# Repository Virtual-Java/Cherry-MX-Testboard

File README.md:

# Cherry-MX-Testboard
A simple single-sided testboard for Cherry-MX-Switches created with EAGLE layout

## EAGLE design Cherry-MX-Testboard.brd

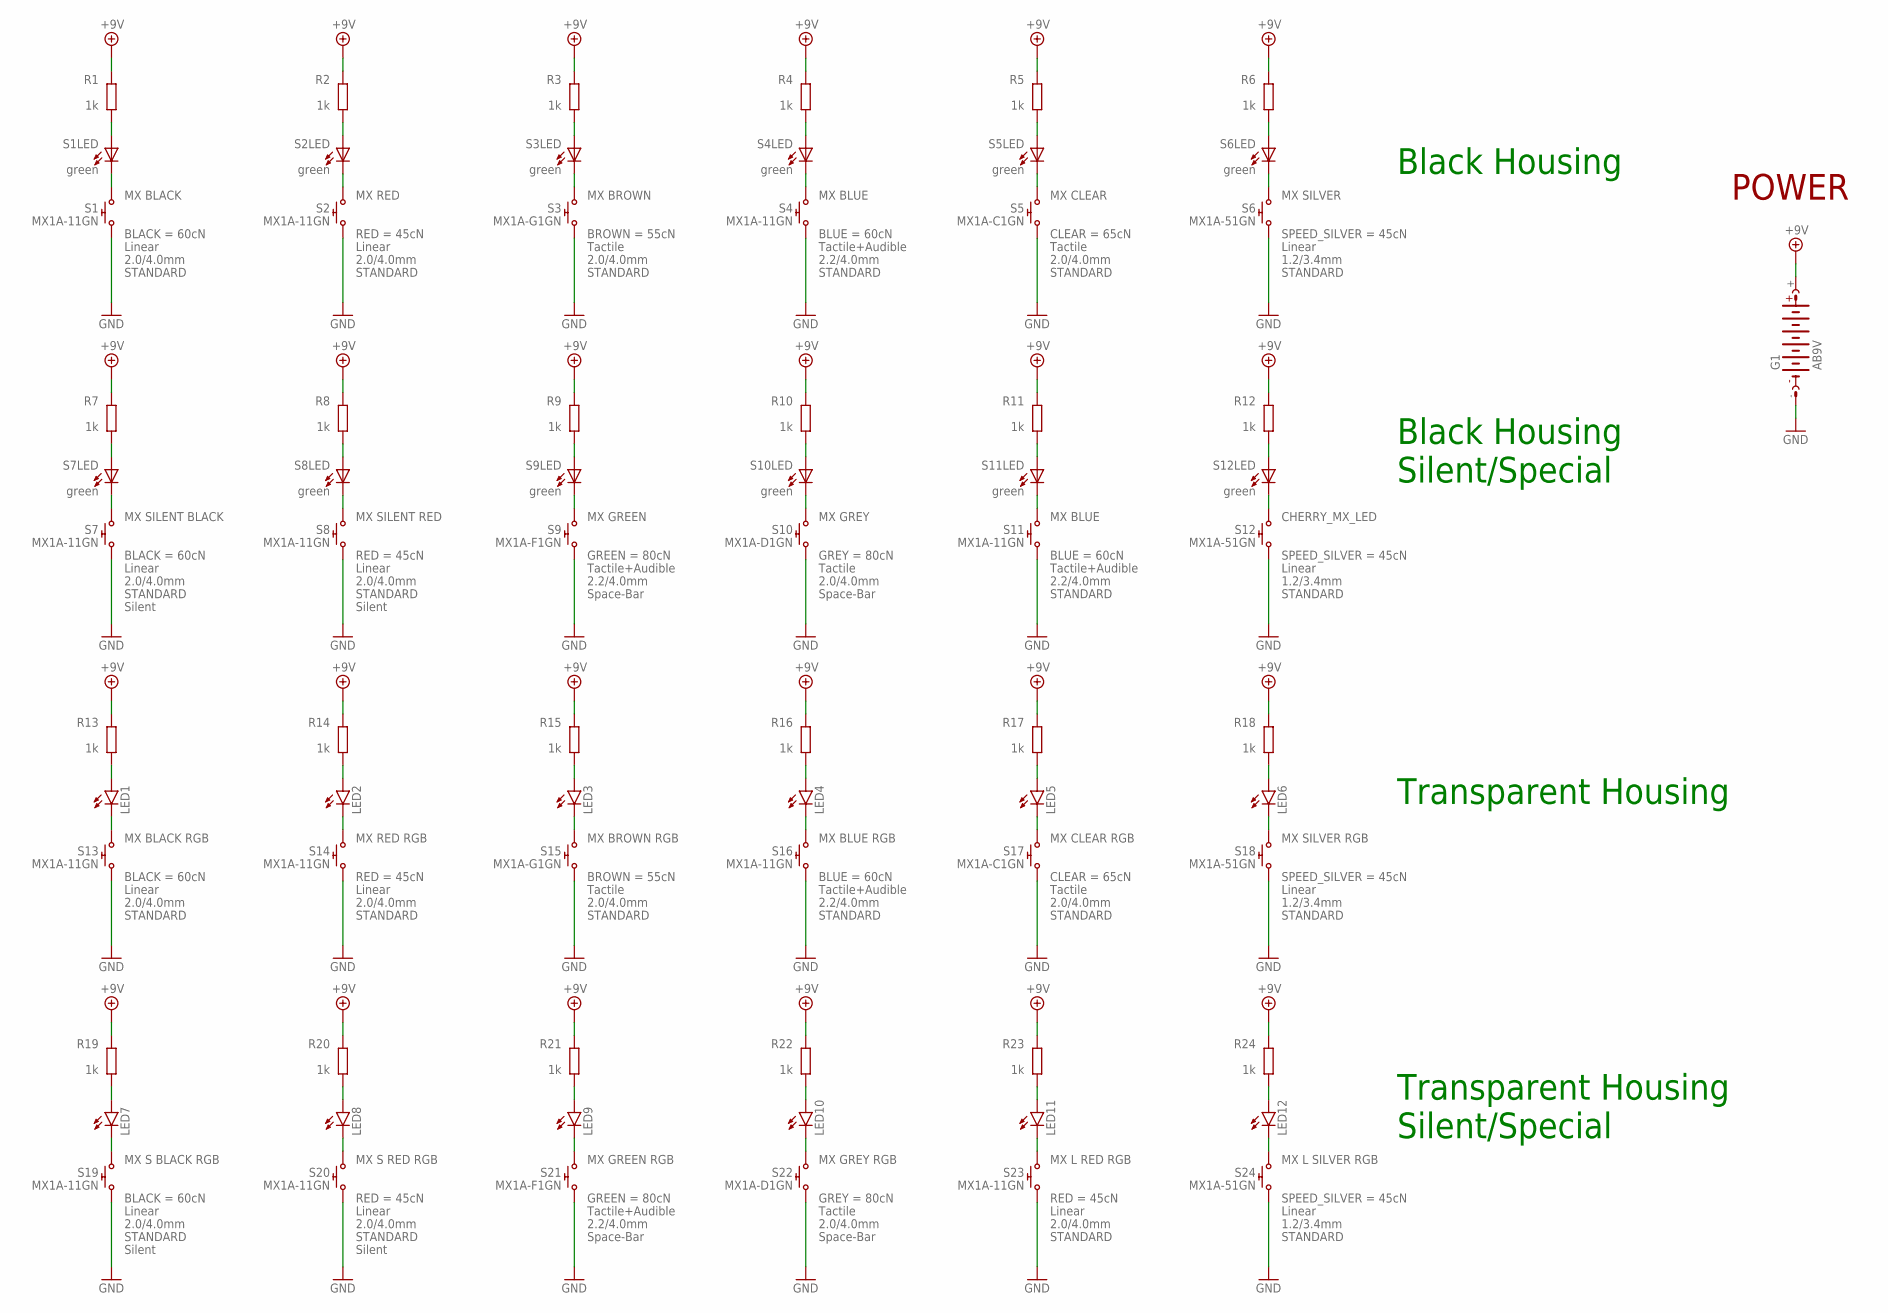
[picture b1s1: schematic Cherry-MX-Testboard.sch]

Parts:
G1: AB9V
LED1, LED2, LED3, LED4, LED5, LED6, LED7, LED8, LED9, LED10, LED11, LED12: LEDMINI-TOP; OSRAM-MINI-TOP-LED
R1, R2, R3, R4, R5, R6, R7, R8, R9, R10, R11, R12, R13, R14, R15, R16, R17, R18, R19, R20, R21, R22, R23, R24: 1k; R0402
S1: MX BLACK; CHERRY_MX_LED
S2: MX RED; CHERRY_MX_LED
S3: MX BROWN; CHERRY_MX_LED
S4, S11: MX BLUE; CHERRY_MX_LED; MOUSER 540_MX1A_E1NW
S5: MX CLEAR; CHERRY_MX_LED
S6: MX SILVER; CHERRY_MX_LED
S7: MX SILENT BLACK; CHERRY_MX_LED
S8: MX SILENT RED; CHERRY_MX_LED
S9: MX GREEN; CHERRY_MX_LED
S10: MX GREY; CHERRY_MX_LED; MOUSER 540_MX1A_21NW
S12: CHERRY_MX_LED
S13: MX BLACK RGB; CHERRY_MX
S14: MX RED RGB; CHERRY_MX
S15: MX BROWN RGB; CHERRY_MX
S16: MX BLUE RGB; CHERRY_MX
S17: MX CLEAR RGB; CHERRY_MX
S18: MX SILVER RGB; CHERRY_MX
S19: MX S BLACK RGB; CHERRY_MX
S20: MX S RED RGB; CHERRY_MX
S21: MX GREEN RGB; CHERRY_MX
S22: MX GREY RGB; CHERRY_MX
S23: MX L RED RGB; CHERRY_MX
S24: MX L SILVER RGB; CHERRY_MX

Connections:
+9V: G1.+, R1.1, R2.1, R3.1, R4.1, R5.1, R6.1, R7.1, R8.1, R9.1, R10.1, R11.1, R12.1, R13.1, R14.1, R15.1, R16.1, R17.1, R18.1, R19.1, R20.1, R21.1, R22.1, R23.1, R24.1
GND: G1.-, S1.S1 (1), S2.S1 (1), S3.S1 (1), S4.S1 (1), S5.S1 (1), S6.S1 (1), S7.S1 (1), S8.S1 (1), S9.S1 (1), S10.S1 (1), S11.S1 (1), S12.S1 (1), S13.S1 (1), S14.S1 (1), S15.S1 (1), S16.S1 (1), S17.S1 (1), S18.S1 (1), S19.S1 (1), S20.S1 (1), S21.S1 (1), S22.S1 (1), S23.S1 (1), S24.S1 (1)
unnamed: S1.L2 (C), S1.S2 (2)
unnamed: S2.L2 (C), S2.S2 (2)
unnamed: R1.2, S1.L1 (A)
unnamed: R2.2, S2.L1 (A)
unnamed: S3.L2 (C), S3.S2 (2)
unnamed: R3.2, S3.L1 (A)
unnamed: S4.L2 (C), S4.S2 (2)
unnamed: R4.2, S4.L1 (A)
unnamed: S9.L2 (C), S9.S2 (2)
unnamed: R9.2, S9.L1 (A)
unnamed: S10.L2 (C), S10.S2 (2)
unnamed: R10.2, S10.L1 (A)
unnamed: S5.L2 (C), S5.S2 (2)
unnamed: R5.2, S5.L1 (A)
unnamed: S6.L2 (C), S6.S2 (2)
unnamed: R6.2, S6.L1 (A)
unnamed: S7.L2 (C), S7.S2 (2)
unnamed: R7.2, S7.L1 (A)
unnamed: S8.L2 (C), S8.S2 (2)
unnamed: R8.2, S8.L1 (A)
unnamed: LED1.C, S13.S2 (2)
unnamed: LED1.A, R13.2
unnamed: LED2.C, S14.S2 (2)
unnamed: LED2.A, R14.2
unnamed: LED3.C, S15.S2 (2)
unnamed: LED3.A, R15.2
unnamed: LED4.C, S16.S2 (2)
unnamed: LED4.A, R16.2
unnamed: LED9.C, S21.S2 (2)
unnamed: LED9.A, R21.2
unnamed: LED10.C, S22.S2 (2)
unnamed: LED10.A, R22.2
unnamed: LED5.C, S17.S2 (2)
unnamed: LED5.A, R17.2
unnamed: LED6.C, S18.S2 (2)
unnamed: LED6.A, R18.2
unnamed: LED7.C, S19.S2 (2)
unnamed: LED7.A, R19.2
unnamed: LED8.C, S20.S2 (2)
unnamed: LED8.A, R20.2
unnamed: LED11.C, S23.S2 (2)
unnamed: LED11.A, R23.2
unnamed: LED12.C, S24.S2 (2)
unnamed: LED12.A, R24.2
unnamed: S11.L2 (C), S11.S2 (2)
unnamed: R11.2, S11.L1 (A)
unnamed: S12.L2 (C), S12.S2 (2)
unnamed: R12.2, S12.L1 (A)

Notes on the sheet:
Black Housing
Black Housing Silent/Special
Transparent Housing
Transparent Housing Silent/Special
POWER

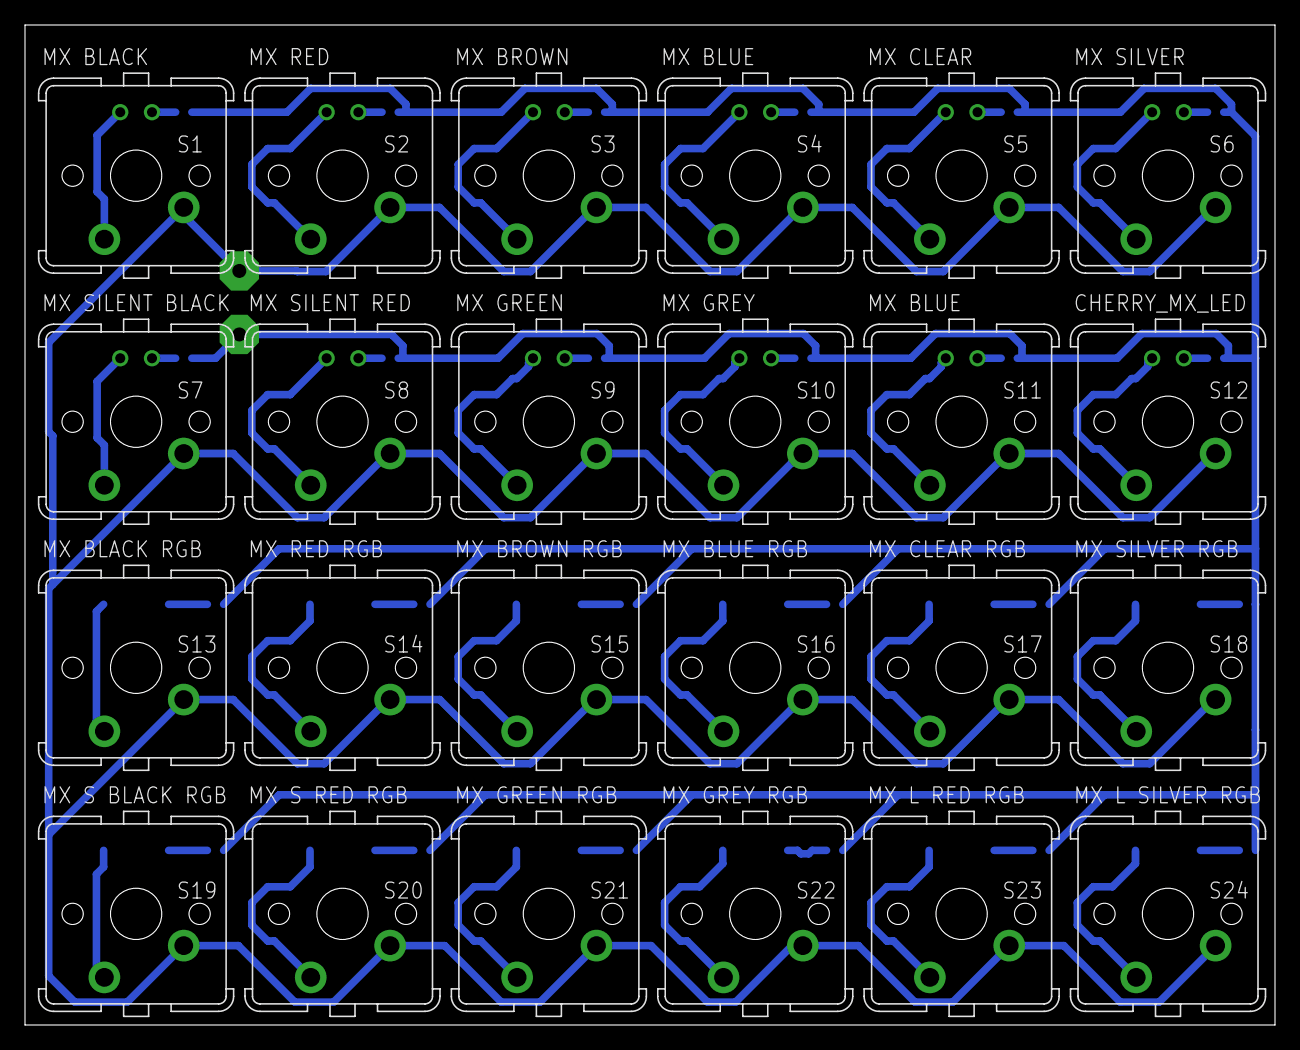
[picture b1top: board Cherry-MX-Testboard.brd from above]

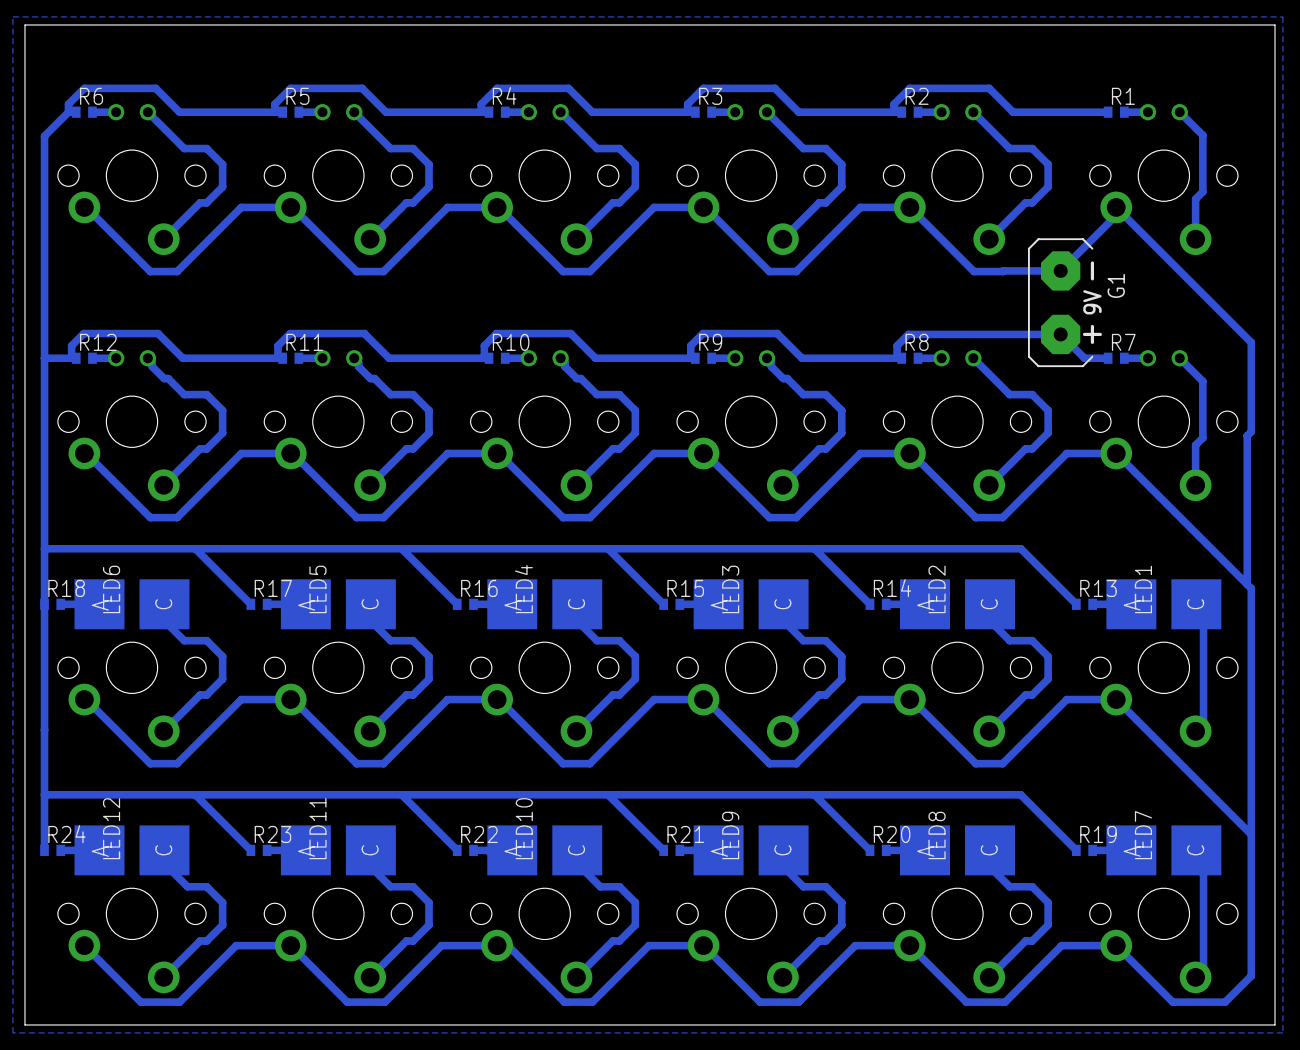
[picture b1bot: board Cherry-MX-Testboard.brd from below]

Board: 2 copper layers, 100.0 x 80.0 mm, 61 parts (37 on the bottom side), 50 nets.

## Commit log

2020-09-01 Add files via upload
    uploaded revision1 of my Testboard for Cherry-MX-Switches
